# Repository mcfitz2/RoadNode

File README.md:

# RoadNode

Low-power OBD-II vehicle telemetry node. Reads standard OBD-II over CAN, integrates vehicle speed into distance, and reports over [MeshCore](https://github.com/meshcore-dev/MeshCore) as a sensor node. See [`plan.md`](plan.md) for the original plan (parts are superseded; its header lists which) and [`docs/meshcore.md`](docs/meshcore.md) for the MeshCore integration notes.

## Layout

- `vendor/MeshCore`: unmodified git submodule, pinned. Never edit it.
- `src/`: RoadNode code (`can/ obd/ vehicle/ storage/ telemetry/ node/`, plus the standalone tools `sniffer/ monitor/ ecusim/`). Only `telemetry/` and `node/` include MeshCore headers.
- `platformio.ini`: env `heltec_v4_roadnode`.

```sh
git clone --recurse-submodules https://github.com/mcfitz2/RoadNode.git
pio run -e heltec_v4_roadnode   # MeshCore sensor firmware
pio run -e heltec_v4_cansniffer # listen-only CAN logger (no MeshCore)
pio run -e heltec_v4_obdmonitor # OBD poll + mileage + NVS, serial output (no MeshCore); transmits OBD requests, see OBD_TRANSMIT_ENABLE in platformio.ini
pio test -d host                # host unit tests
```

## Hardware

- **Board:** Heltec WiFi LoRa 32 **V4.3**, no OLED (KCT8103L PA, 2 MB PSRAM). Uses MeshCore's plain `heltec_v4` pin map, not `heltec_v4_r8`. Verify the "V4.3" silkscreen on arrival.
- **CAN transceiver:** SN65HVD230 (3.3 V). No 120 ohm termination: we attach to an existing bus.

### CAN wiring

| Function | Heltec V4 GPIO | SN65HVD230 | OBD-II pin |
| --- | --- | --- | --- |
| CAN TX | GPIO3 | TXD | |
| CAN RX | GPIO4 | RXD | |
| Ground | GND | GND | 4 or 5 |
| Logic power | 3.3 V | VCC | |
| CAN High | | CANH | 6 |
| CAN Low | | CANL | 14 |

Power depends on the build:

- **Breadboard:** power the board from USB-C and leave OBD pin 16 (+12 V) unconnected.
- **Carrier PCB** ([hardware/carrier/](hardware/carrier/)): powered from OBD pin 16 through a fuse, TVS clamp, 5.2 V buck and low-voltage cutoff. There is no battery. The carrier powers the transceiver from VEXT (GPIO36), not the 3.3 V pin.

The env does not set MeshCore's `ENV_PIN_SDA/SCL`, which the stock `heltec_v4_sensor` env points at GPIO3/4. Keep it that way.

### Pins in use by the board (V4 / V4.3, per MeshCore's `heltec_v4` variant)

| GPIO | Function |
| --- | --- |
| 0 | User button |
| 1 | Battery voltage read |
| 2, 5, 7, 46 | LoRa PA / FEM control |
| 8-14 | SX1262 (NSS 8, SCLK 9, MOSI 10, MISO 11, RST 12, BUSY 13, DIO1 14) |
| 17, 18, 21 | OLED SDA, SCL, RST (free on the no-OLED board, but avoid) |
| 35 | TX LED |
| 36 | VEXT enable (active HIGH) |
| 37 | Battery ADC control |
| 34, 38, 39, 42 | GNSS enable (active LOW), RX, TX, reset (active LOW). Reserved for GPS |
| 40, 41 | Plan reserved these for GNSS wake/PPS; unconfirmed against the Heltec schematic |

R8 boards differ (VEXT=40, GNSS enable=42, LED=46, octal PSRAM on GPIO33-37). Not our board.

## Design principles

1. Do not depend on proprietary CAN decoding for basic mileage.
2. Use standard OBD-II wherever possible.
3. Calculate distance locally.
4. Persist mileage independently of MeshCore.
5. Do not transmit raw CAN traffic over MeshCore.
6. Use the same generic OBD-II settings for every vehicle; no per-vehicle profiles.
7. Keep OBD read-only: modes 01 and 09 only, never mode 04 (clear codes).
8. Design parked power consumption as a first-class requirement.
9. Reserve the V4 GNSS pins.
10. Keep the CAN hardware electrically independent from the LoRa hardware.
11. Start with listen-only CAN monitoring before transmitting anything to a vehicle.
12. Test the 2006 RAV4 first; it is the reference implementation.

## Releases

CI uploads a flashable `firmware-merged.bin` for every push (workflow artifact `roadnode-heltec_v4-<sha>`). Pushing a
tag that starts with `v` (for example `git tag v0.1.0 && git push origin v0.1.0`) also creates a GitHub release and
attaches `roadnode-heltec_v4-<tag>.bin`. Flash at offset 0: `esptool.py write_flash 0x0 roadnode-heltec_v4-<tag>.bin`.

## License

MIT, see `LICENSE`. MeshCore (`vendor/MeshCore`) and files derived from it are covered by its own MIT notice: see `THIRD_PARTY_NOTICES.md`.

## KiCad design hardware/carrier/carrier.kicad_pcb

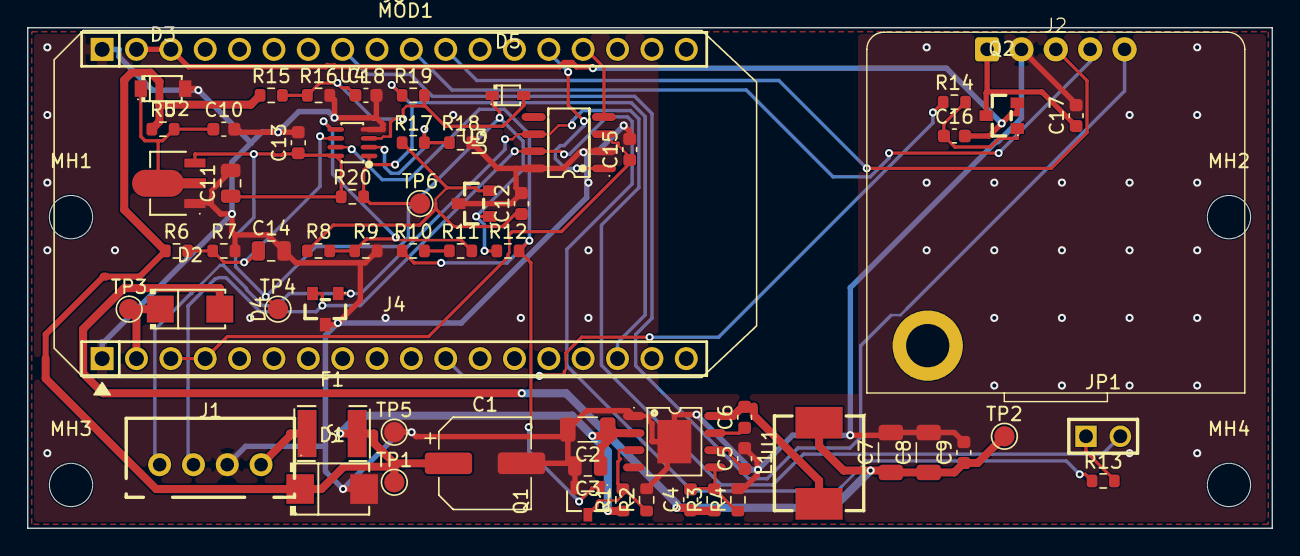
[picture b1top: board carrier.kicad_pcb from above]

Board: 2 copper layers, 92.0 x 37.0 mm, 68 parts (0 on the bottom side), 33 nets.

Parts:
C1: 47u 50V; CP_Elec_6.3x7.7
C2: 10u 50V; C_1206_3216Metric
C3: 100n 100V; C_0805_2012Metric
C4: 10p C0G; C_0603_1608Metric
C5, C10, C17: 1u; C_0603_1608Metric
C6, C9, C12, C13, C15, C18: 100n; C_0603_1608Metric
C7, C8: 22u 25V; C_1206_3216Metric
C11, C14: 10u; C_0805_2012Metric
C16: 10n; C_0603_1608Metric
D1: SMBJ26A; SMB_L4.6-W3.6-LS5.3-RD
D2: SS34; SMA_L4.3-W2.6-LS5.2-RD
D3: BZT52C24; SOD-123_L2.7-W1.6-LS3.7-RD
D4: PESD1CAN; SOT-23_L2.9-W1.3-P1.90-LS2.4-BR
D5: 1N4148WS; SOD-323_L1.8-W1.3-LS2.5-RD
F1: 1.5A hold; F1812
J1: OBD pigtail; CONN-TH_B4B-XH-A-LF-SN
J2: GT-U7; GT-U7_THT
J4: Heltec JP4; HDR-TH_18P-P2.54-V-F
J5: Heltec JP5; HDR-TH_18P-P2.54-V-F
JP1: TERM 120R; HDR-TH_2P-P2.54-V-M_2
L1: 15u; IND-SMD_L7.3-W6.8
MH1, MH2, MH3, MH4: M3; MountingHole_3.2mm_M3
MOD1: Heltec WiFi LoRa 32 V4.3 (on sockets); Heltec_WiFi_LoRa32_V4
Q1: 2N7002; SOT-23-3_L2.9-W1.3-P1.90-LS2.4-BR
Q2: AO3401A; SOT-23_L2.9-W1.3-P1.90-LS2.4-BR
R1, R6: 3M; R_0603_1608Metric
R2, R7, R18: 750k; R_0603_1608Metric
R3, R12, R15, R20: 1M; R_0603_1608Metric
R4: 240k; R_0603_1608Metric
R5, R14: 10k; R_0603_1608Metric
R8: 510k; R_0603_1608Metric
R9, R10, R11, R19: 10M; R_0603_1608Metric
R13: 120; R_0603_1608Metric
R16: 220k; R_0603_1608Metric
R17: 47k; R_0603_1608Metric
TP1: VIN; TestPoint_Pad_D1.5mm
TP2: V5R; TestPoint_Pad_D1.5mm
TP3: H5V; TestPoint_Pad_D1.5mm
TP4: V3A; TestPoint_Pad_D1.5mm
TP5: GND; TestPoint_Pad_D1.5mm
TP6: WAKE; TestPoint_Pad_D1.5mm
U1: LMR36520ADDAR; POWERPAD-SO-8_L4.9-W3.9-P1.27-LS6.0-BL-EP
U2: HT7533-1; SOT-89-3_L4.5-W2.5-P1.50-LS4.2-BR
U3: REF3325 2.5V; SOT-23_L2.9-W1.3-P1.90-LS2.4-BR
U4: TLV7022DDFR; SOT-23-8_L2.9-W1.6-P0.65-LS2.8-BR
U5: SN65HVD230DR; SOIC-8_L4.9-W3.9-P1.27-LS6.0-BL

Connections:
3V3: C16.2, J5.2, J5.3, Q2.2
BOOT: C6.1, U1.7
BUCK_VCC: C5.1, U1.6
CANH: D4.2, J1.3, R13.1, U5.7
CANL: D4.1, J1.4, JP1.2, U5.6
CAN_RX: J5.15, U5.4
CAN_TERM: JP1.1, R13.2
CAN_TX: J5.14, U5.1
CAR_ON: J4.16, R19.1, R20.2, TP6.1, U4.1
EN: Q1.3, R1.2, R2.1, U1.3
FB: C4.2, R3.2, R4.1, U1.5
GND: C1.2, C2.2, C3.2, C5.2, C7.2, C8.2, C9.2, C10.2, C11.2, C12.2, C13.2, C14.2, C15.2, C17.2, C18.2, D1.2, D3.2, D4.3, J1.2, J2.2, J4.1, J5.1, Q1.2, R2.2, R4.2, R7.2, R9.2, R16.2, R18.2, TP5.1, U1.1, U1.9, U2.1, U3.3, U4.4, U5.2, U5.8
GNSS_EN_N: J4.11, R14.1
GNSS_G: C16.1, Q2.1, R14.2
GNSS_VCC: C17.1, J2.1, Q2.3
GPS_PPS: J2.5, J5.8
GPS_RXD: J2.3, J5.11
GPS_TXD: J2.4, J5.10
H_5V: D2.1, J4.2, TP3.1
SW: C6.2, L1.1, U1.8
UV_HYS: R10.2, R11.1
UV_LOW: Q1.1, R10.1, R12.2, U4.7
UV_REF: R8.2, R9.1, R11.2, U4.5
UV_TAP: C14.1, R6.2, R7.1, U4.6
V3A: C11.1, C13.1, D5.1, R12.1, R20.1, TP4.1, U2.3, U3.1, U4.8
V3A_IN: C10.1, D3.1, R5.2, U2.2
V5R: C4.1, C7.1, C8.1, C9.1, D2.2, L1.2, R3.1, TP2.1
VEXT: C15.1, J4.3, J4.4, U5.3
VIN: C1.1, C2.1, C3.1, D1.1, F1.2, R1.1, R5.1, R6.1, R15.1, TP1.1, U1.2
VREF: C12.1, R8.1, R17.1, U3.2
V_CAR: F1.1, J1.1
V_TAP: C18.1, D5.2, R15.2, R16.1, R19.2, U4.3
WAKE_REF: R17.2, R18.1, U4.2

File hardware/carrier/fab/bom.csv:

Comment,Designator,Footprint,LCSC
47u 50V,C1,CP_Elec_6.3x7.7,C970679
1u,"C10,C17,C5",C_0603_1608Metric,C15849
10u,"C11,C14",C_0805_2012Metric,C15850
100n,"C12,C13,C15,C18,C6,C9",C_0603_1608Metric,C14663
10n,C16,C_0603_1608Metric,C57112
10u 50V,C2,C_1206_3216Metric,C13585
100n 100V,C3,C_0805_2012Metric,C28233
10p C0G,C4,C_0603_1608Metric,C1634
22u 25V,"C7,C8",C_1206_3216Metric,C12891
SMBJ26A,D1,SMB_L4.6-W3.6-LS5.3-RD,C19077580
SS34,D2,SMA_L4.3-W2.6-LS5.2-RD,C8678
BZT52C24,D3,SOD-123_L2.7-W1.6-LS3.7-RD,C173422
1N4148WS,D5,SOD-323_L1.8-W1.3-LS2.5-RD,C2128
2N7002,Q1,SOT-23-3_L2.9-W1.3-P1.90-LS2.4-BR,C8545
AO3401A,Q2,SOT-23_L2.9-W1.3-P1.90-LS2.4-BR,C15127
3M,"R1,R6",R_0603_1608Metric,C23156
10M,"R10,R11,R19,R9",R_0603_1608Metric,C7250
1M,"R12,R15,R20,R3",R_0603_1608Metric,C22935
120,R13,R_0603_1608Metric,C22787
10k,"R14,R5",R_0603_1608Metric,C25804
220k,R16,R_0603_1608Metric,C22961
47k,R17,R_0603_1608Metric,C25819
750k,"R18,R2,R7",R_0603_1608Metric,C23240
240k,R4,R_0603_1608Metric,C4197
510k,R8,R_0603_1608Metric,C23192
LMR36520ADDAR,U1,POWERPAD-SO-8_L4.9-W3.9-P1.27-LS6.0-BL-EP,C2879422
HT7533-1,U2,SOT-89-3_L4.5-W2.5-P1.50-LS4.2-BR,C14289
REF3325 2.5V,U3,SOT-23_L2.9-W1.3-P1.90-LS2.4-BR,C69039
TLV7022DDFR,U4,SOT-23-8_L2.9-W1.6-P0.65-LS2.8-BR,C2862588
SN65HVD230DR,U5,SOIC-8_L4.9-W3.9-P1.27-LS6.0-BL,C12084

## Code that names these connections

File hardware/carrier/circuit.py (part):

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gnd.drive = 3  # POWER

# ---------------------------------------------------------------- nets
v_car = Net("V_CAR")  # OBD pin 16 via pigtail, unfused
vin = Net("VIN")  # fused, clamped
v5r = Net("V5R")  # buck output, on unless the low-voltage cutoff holds the buck off
h5v = Net("H_5V")  # Heltec header 5V pin (= its USB VBUS net)
v3a = Net("V3A")  # always-on 3.3 V from VIN: comparators and pull-ups, up while the buck is off
vref = Net("VREF")  # 2.5 V precision reference for both comparator thresholds
v3v3 = Net("3V3")  # Heltec always-on 3.3 V (header)
vext = Net("VEXT")  # Heltec switched 3.3 V (GPIO36, active level per MeshCore heltec_v4: HIGH)
canh, canl = Net("CANH"), Net("CANL")
for n in (vin, v5r, v3v3, vext):
    n.drive = 3
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# H_J3 = Heltec JP5 (GND, 3V3, 3V3, 37, 46, 45, 42, 41, 40, 39, 38, 1, 2, 3, 4, 5, 6, 7)
h_j2 = ic("KH-2.54FH-1X18P-H8.5", "Heltec JP4", "HDR-TH_18P-P2.54-V-F", "C2905422", ref="J4")
h_j3 = ic("KH-2.54FH-1X18P-H8.5", "Heltec JP5", "HDR-TH_18P-P2.54-V-F", "C2905422", ref="J5")
gnss_en_n = Net("GNSS_EN_N")  # GPIO34 VGNSS_Ctrl, 10k pull-up on the Heltec
h_j2[1] += gnd
h_j2[2] += h5v
h_j2[3, 4] += vext
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gps_pps, gps_txd, gps_rxd = Net("GPS_PPS"), Net("GPS_TXD"), Net("GPS_RXD")
h_j3[1] += gnd
h_j3[2, 3] += v3v3
h_j3[8] += gps_pps  # GPIO41
h_j3[10] += gps_txd  # GPIO39 = MCU RX (MeshCore Serial1.setPins(PIN_GPS_TX, PIN_GPS_RX))
h_j3[11] += gps_rxd  # GPIO38 = MCU TX
h_j3[14] += can_tx  # GPIO3
h_j3[15] += can_rx  # GPIO4

NO_CONNECT_J2 = [5, 6, 7, 8, 9, 10, 12, 13, 14, 15, 17, 18]
NO_CONNECT_J3 = [4, 5, 6, 7, 9, 12, 13, 16, 17, 18]

# ---------------------------------------------------------------- CAN
# Powered from VEXT so it draws nothing while the Heltec sleeps; firmware switches
# VEXT on before starting TWAI and floats GPIO3 before switching it off (PROJ-685).
u_can = ic("SN65HVD230DR", "SN65HVD230DR", "SOIC-8_L4.9-W3.9-P1.27-LS6.0-BL", "C12084")
u_can["VCC"] += vext
u_can["GND"] += gnd
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d_clamp["A"] += v_tap
d_clamp["K"] += v3a
v3a & R("1M", R_LCSC["1M"]) & car_on  # open drain, never above 3.3 V
h_j2[16] += car_on  # GPIO21
tp = part("Connector", "TestPoint", "WAKE", "TestPoint:TestPoint_Pad_D1.5mm", "", "TP")
tp[1] += car_on

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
